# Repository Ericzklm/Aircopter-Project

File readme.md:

# Aircopter Project

#### To see a more updated version of this project, see Aircopter-Project-v2

This project was done in association with the IEEE Student Branch on the UCLA campus.
This is the first iteration of the project.

The goal of the project was to: 1. Design and assemble a custom PCB for a drone,
2. Write a program to hover the drone, then fly the drone. Because of the nature
of the project, the PCB was required to be small and compact (meaning SMD soldering
was needed) and the program needed to be quick and responsive.

### Hardware Selection Choices:

**MCU**: The main chip is the model STM32F405. This was chosen for its ideal balance
between size and functionality. It is able to support all the needed sensors and
motor drivers for our drone and can be powered by a 3.3v supply which closely
matches the 3.7v of standard drone batteries (3.7v is stepped down to 3.3 using
a voltage regulator). Additionally, this chip was more ideal than other chips of
similar style because it handles floating point calculations better which allows
for simplicity and efficiency when writing the program.

**Voltage Regulator**: The voltage regulator used is the Richtek RT6150B-33GQW which
was choosen for its size and the use of buck-boost as well as operating within
the voltage supplied by the battery. The voltage regulator was simple to use
and had a well documented spec sheet in comparison to other choices but used
exposed pads instead of pins for soldering which proved to be the biggest
challenge in assembly.

**Wireless Module**: The wireless module used is the nrf24l01 which is standard, easy
to use, and familiar so we used it in this application since it fits well with the
acclerometer module.

**Accelerometer/Gyroscope**: The module used is the mpu6050 which is standard, easy to
use, and familiar so we used it in this application since it fits well with the
wireless module.

**Oscillator**: The oscillator used is the Abracon ABLS-12.000MHZ-B2-T which is a
crystal oscillator at 12 mHz which was suitable for the MCU. This specific oscillator
was choosen because the documentation was clear on how to configure the module. A
SMD mounted version was chosen.

**Passive Components**: For the resistors, capacitors, and inductors, we primarily
used parts with the package size 0603 which would fit the board without being
overly difficult to solder. Each piece was checked for its operating voltages as 
well as the operating temperatures to make sure no issues would arise.

### Hardware Design Choices:

**General**: The board is composed of two sides where each side has routes and vias to
connect the different components. The negative spaces are occupied by polygons. On
the front side, there is a seperate polygon for 3.7v and 3.3v that are connected
by the voltage regulator that steps the voltage down. On the back, there are seperate
polygons for ground and motor ground. Motor ground is seperated because the motor
ground will have more noise and we dont want to include the added noise in other
components.

**Battery**: The battery is a generic 3.7v drone battery that connects via a JST connector.
A couple of decoupling capacitors are placed directly alongside the female header on the 
board. It is placed as close as possible to the JST headers that connect to the motors
as we need to decrease the resistance by having a large polygon that gives a direct
connection.

**Voltage Regualtor**: The voltage regulator is placed between the 3.7v and 3.3v planes
such that the two are completely isolated. There is an inductor included directly
alongside the voltage regulator as recommended by the spec sheet. A few decoupling
capcitors are also included.

**Voltage Divider**: A couple resistors are used to form a voltage divider that gives
an analog input to the MCU which can be used to read battery status. These resistors
are placed such that they do not have signficant effect on the routing or the polygons.

**Programmer**: The programmer is a set of 4 male header pins that allow us to upload 
programs to the drone through a seperate board. It is placed in the top left corner
for easy access and to make sure the sensors do not cover the pins.

**Reset Button**: The switch is placed such that there is easy access to it while not having
the placement disrupt any polygons. A capacitor is included to stabalize the signal sent
to the MCU.

**Oscillator**: The oscillator is placed as close to the MCU as possible to reduce unwanted
affects on the traces. As indicated by the spec sheet, there are two resistors that
ground both the input and output of the oscillator.

**Motors**: The motors connectorsare placed along the top of the board for easy access when 
plugging in the JST connectors. Each motor is paired with a motor driver circuit including
a diode and a mosfet. These components are located as close as possible to each other and 
have the thickest possible traces to decrease resistance. Each motor driver is connected
to a PWM capable pin located on the MCU.

**MCU**: The MCU is placed in a central position on the board as it needs to connect to most
components on the board. It is turned such that the length of traces is optimized and
components that are more essential to have short traces are accounted for. The decoupling
capacitors for the MCU are located on the opposite side of it and are connected by vias.

**Sensor Modules**: Both modules are lifted above the board using headers and because they
sit at similar heights above the board, their placement does not overlap. The decoupling
capacitors are placed near the respective pins on the MCU.

### Hardware Flaws:

**Not Space Efficient**: A few choices made the board more cluttered and more difficult to
make routes and polygons. The motor driver circuits could have made better use of the
two sided board as in the current configuration, they occupied a quarter of the board.
The oscillator would have benefitted from being a through-hole component as the soldering
pads and capacitors occupied a lot of space. In a different part of the board. There is
a lot of open space meaning there are parts of the board where there are unnecessary
bottlenecks.

**Accelerometer Placement**: The idea behind the accelerometer and wireless module not
overlapping is that since they were both lifted off the main board at a similar height,
they could not occupy the same space. However, the accelerometer lies slightly lower
than the wireless module so it can be moved closer the the MCU, allowing for shorter
traces.

**Bottlenecks**: There are some moderate bottlenecks in this design and also places where
the polygons have rather indirect routes. For example, some components rely on power
that comes gaps in the MCU which signficantly bottlenecks the polygons. The 3.3v 
needed by the wireless module comes from a couple vias and a route used as a bridge
rather than having a direct connection as it is cut off from the 3.3v polygon.

**Voltage Regulator**: The voltage regulator was small and simple but due to the exposed
pad design and its small size, was a pain to solder. This ended up being by far the
biggest hiccup in the assembly of the board and required backup components.

**Decoupling Capacitors**: The decoupling capacitors are not optimally placed in every
case but rather are placed to prevent bottlenecks. Capacitors for certain components
are placed near the MCU rather than the component itself.

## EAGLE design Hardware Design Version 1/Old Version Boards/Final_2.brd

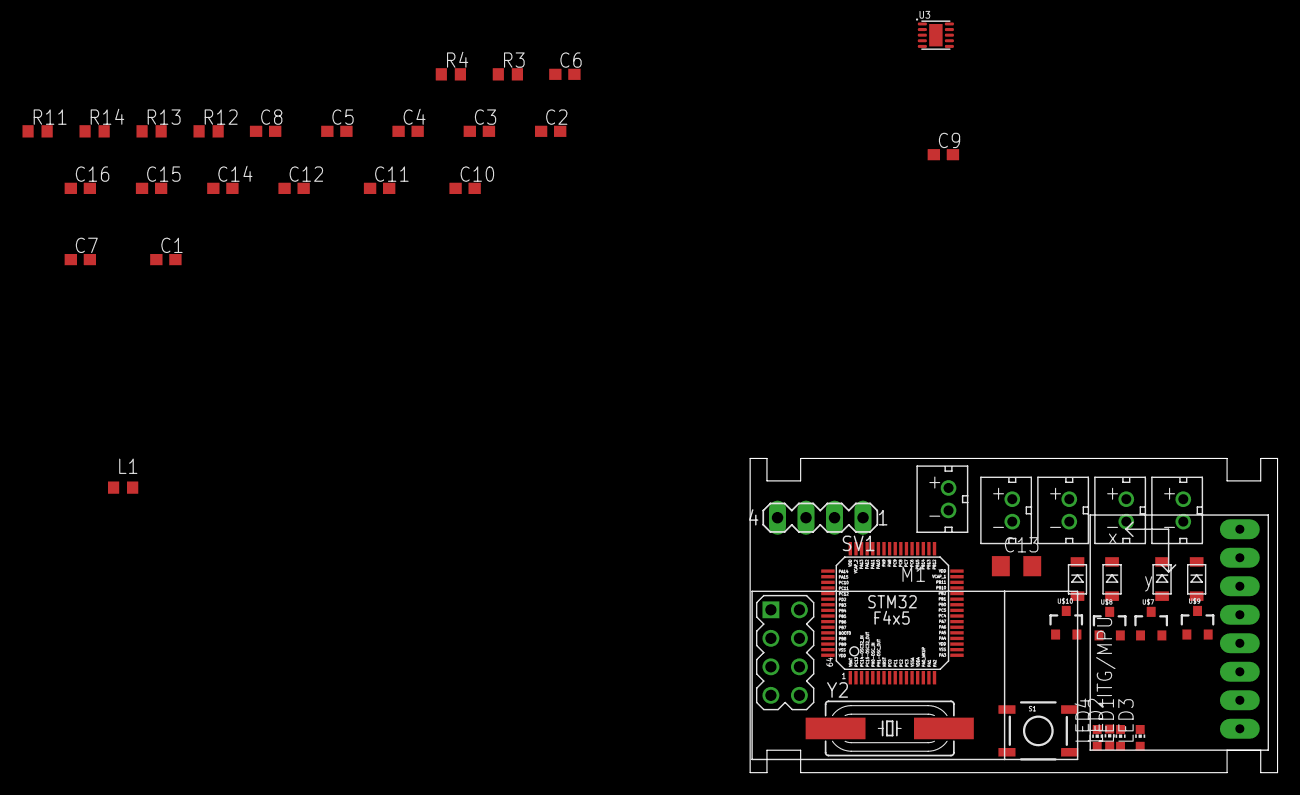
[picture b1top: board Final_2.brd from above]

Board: 2 copper layers, 47.0 x 28.0 mm, 47 parts (0 on the bottom side), 36 nets, no tracks yet.

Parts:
C1, C7, C9, C10, C11, C12: 100nF; C0603
C2, C8: 10uF; C0603
C3: 22uF; C0603
C4, C5: 16pF; C0603
C6: 1uF; C0603
C13: 100uF; C1206
C14, C15: 2.2uF; C0603
C16: 4.7uF; C0603
L1: 2.2uH; L0603
LED1, LED4: Blue; CHIP-LED0603
LED2, LED3: Green; CHIP-LED0603
M1: WIRELESS-NRF24L01
R3, R4: 10k; R0603
R11, R12, R13, R14: 1k; R0603
S1: SWITCH-MOMENTARY-2SMD; TACTILE-SWITCH-SMD
SV1: MA04-1
U2: GY-521MPU6050; GY-521
U3: RT6150B-33GQW; SON50P250X250X80-11N
U$1: STM32F405/415_LQFP64
U$2, U$3, U$4, U$5, U$6: JST_CONNECTOR_FEMALE
U$7, U$8, U$9, U$10: N-CHANNEL-MOSFET-IRLML6244TRPBF; SOT23-3
U$11, U$12, U$13, U$14: DB2W40300L; MINI2-F3-B
Y2: 12MHz; HC49UP

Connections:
3.7V: C2.2, C13.1, R3.2, U3.5, U3.6, U3.7, U3.8, U$2.+, U$3.+, U$4.+, U$5.+, U$6.+, U$11.NEG, U$12.NEG, U$13.NEG, U$14.NEG
ANALOG: R3.1, R4.2, U$1.PA1, U$1.PB1
CE: M1.3, U$1.PA7
CSN: M1.4, U$1.PA6
GND: C1.1, C2.1, C3.2, C4.2, C5.2, C6.1, C7.1, C8.1, C9.1, C10.1, C11.1, C12.1, C13.2, C14.2, C15.1, C16.1, LED1.C, LED2.C, LED3.C, LED4.C, M1.1, R4.1, S1.1, SV1.4, U2.GND, U3.3, U3.9, U3.11, U$1.BOOT0, U$1.VSSA, U$1.VSS_0, U$1.VSS_1, U$2.-, U$7.2, U$8.2, U$9.2, U$10.2
LED_MISO: R14.1, U$1.PC9
LED_PWR: R11.1, U$1.PC6
LED_RST: R12.1, U$1.PC7
LED_SWDIO: R13.1, U$1.PC8
MISO: M1.7, U$1.PC11
MOSI: M1.6, U$1.PC12
unnamed: L1.2, U3.4
unnamed: L1.1, U3.2
unnamed: U$3.-, U$9.3, U$11.POS
unnamed: U$5.-, U$8.3, U$12.POS
unnamed: U$4.-, U$7.3, U$13.POS
unnamed: U$6.-, U$10.3, U$14.POS
unnamed: LED1.A, R11.2
unnamed: LED4.A, R12.2
unnamed: LED2.A, R13.2
unnamed: LED3.A, R14.2
unnamed: C15.2, U$1.VCAP_1
unnamed: C14.1, U$1.VCAP_2
OSC_IN: C5.1, U$1.PH0, Y2.2
OSC_OUT: C4.1, U$1.PH1, Y2.1
RESET: C6.2, S1.3, SV1.3, U$1.NRST
SCK: M1.5, U$1.PC10
SCL: U2.SCL, U$1.PB10
SDA: U2.SDA, U$1.PB11
SWCLK: SV1.1, U$1.PA14
SWDIO: SV1.2, U$1.PA13
TIM1: U$1.PA8, U$10.1
TIM2: U$1.PA9, U$8.1
TIM3: U$1.PA10, U$7.1
TIM4: U$1.PA11, U$9.1
VOUT: C1.2, C3.1, C7.2, C8.2, C9.2, C10.2, C11.2, C12.2, C16.2, M1.2, U2.VCC, U3.1, U3.10, U$1.VDDA, U$1.VDD_0, U$1.VDD_1, U$1.VDD_2, U$1.VDD_3

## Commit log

2020-07-10 Version 1 Hardware Design Files Added
2020-08-02 Documentation on hardware selection
2020-08-06 Updated Documentation on Design Choices and Flaws
2020-08-08 Added Program Files.
2020-08-13 Added Schematic Image.
